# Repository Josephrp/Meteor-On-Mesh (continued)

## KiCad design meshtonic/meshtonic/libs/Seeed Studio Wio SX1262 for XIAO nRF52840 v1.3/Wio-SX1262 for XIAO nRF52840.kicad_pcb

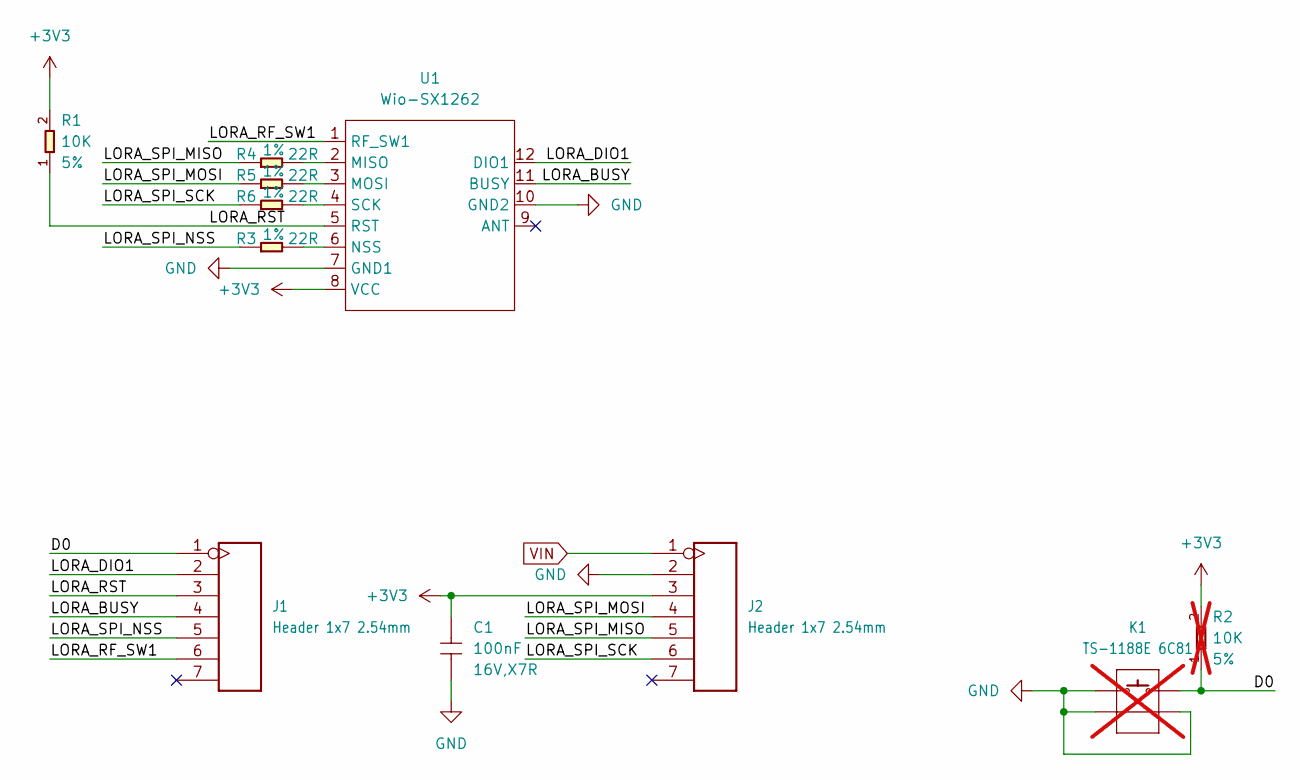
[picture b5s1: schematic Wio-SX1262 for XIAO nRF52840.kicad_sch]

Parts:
C1: 100nF; C0402; Voltage Rating 16V,X7R; MPN CC0402KRX7R7BB104
J1, J2: Header 1x7 2.54mm; H7-2.54; Part Type Header
K1: TS-1188E 6C81; SW4-SMD-7.0X3.5X3.5MM-90D; MPN TS-1188E 6C81; not fitted
R1: 10K; R0402; Power Rating 5%; MPN RC0402JR-0710KL
R2: 10K; R0402; Power Rating 5%; MPN RC0402JR-0710KL; not fitted
R3, R4, R5, R6: 22R; R0402; Power Rating 1%; MPN RC0402FR-0722RL
U1: Wio-SX1262; MODULE12P-1.27-11X11.6MM; MPN Wio-SX1262

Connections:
+3V3: C1.1, J2.3, R1.2, R2.2, U1.8 (VCC)
/D0: J1.1, K1.2, R2.1
/LORA_BUSY: J1.4, U1.11 (BUSY)
/LORA_DIO1: J1.2, U1.12 (DIO1)
/LORA_RF_SW1: J1.6, U1.1 (RF_SW1)
/LORA_RST: J1.3, R1.1, U1.5 (RST)
/LORA_SPI_MISO: J2.5, R4.1
/LORA_SPI_MOSI: J2.4, R5.1
/LORA_SPI_NSS: J1.5, R3.1
/LORA_SPI_SCK: J2.6, R6.1
GND: C1.2, J2.2, K1.1, K1.3 (S1), K1.4 (S2), U1.7 (GND1), U1.10 (GND2)
unnamed: R4.2, U1.2 (MISO)
unnamed: R5.2, U1.3 (MOSI)
unnamed: R3.2, U1.6 (NSS)
unnamed: R6.2, U1.4 (SCK)
VIN: J2.1

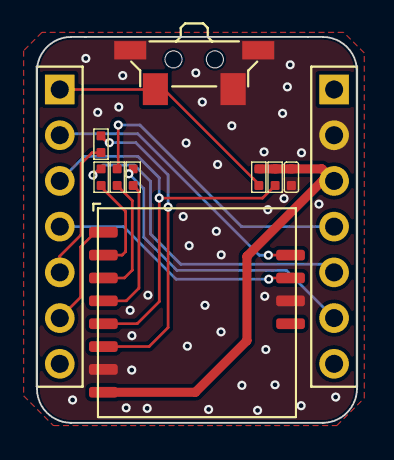
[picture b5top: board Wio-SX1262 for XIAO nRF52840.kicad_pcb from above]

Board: 2 copper layers, 17.8 x 21.4 mm, 11 parts (0 on the bottom side), 15 nets.

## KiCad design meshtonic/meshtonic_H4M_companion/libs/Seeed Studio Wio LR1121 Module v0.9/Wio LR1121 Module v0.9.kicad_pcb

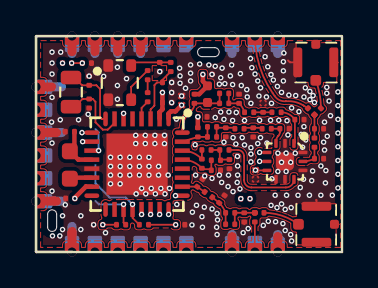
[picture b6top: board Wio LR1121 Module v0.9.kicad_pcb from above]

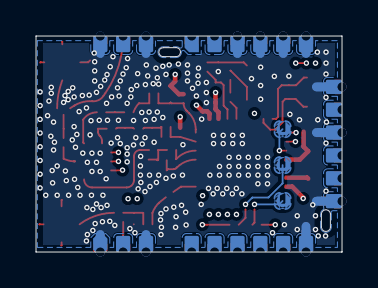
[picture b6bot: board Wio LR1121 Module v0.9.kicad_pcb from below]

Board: 4 copper layers, 17.0 x 12.0 mm, 69 parts (3 on the bottom side), 47 nets.

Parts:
C1, C2, C3, C4, C5, C6, C7, C8, C9, C11, C12, C13, C14, C15, C18, C19, C20, C22, C24, C25, C26, C27, C28, C29, C30, C31, C32, C33, C34, C35, C36, C37, C38, C39, C40, C41, C42, C43: C0201
FB1: L0201
J1, J2: U-FL4P-SMD-1_7X1_7X1_0MM
L1: L0402
L2, L3, L5, L6, L7, L8, L9, L10, L11, L13: L0201
L12: L0603
OSC1: X4_SMD_2_5X2_0MM
R1, R2, R3, R4, R5, R7, R8, R9: R0201
TP23, TP24, TP25: TP35S_SMD
U1: QFN12_0D5_2X2X0_55MM
U2: QFN32_0D5_5X5MM_EP3P3MM
U3: MODULE24_1D27_17X12MM
X1: X2_SMD_2X1_2MM

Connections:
2.4G_RF: C43.2, U3.2
GND_POWER: C3.2, C4.2, C5.2, C6.2, C7.2, C8.2, C11.2, C12.2, C13.2, C14.2, C15.2, C18.2, C19.2, C22.2, C25.2, C26.2, C28.2, C29.2, C30.2, C31.2, C32.2, C33.2, C35.2, C36.2, C37.2, C38.2, C40.2, C42.2, J1.2, J1.3, J1.4, J2.2, J2.3, J2.4, OSC1.1, OSC1.2, U1.2, U1.7, U1.8, U1.10, U1.12, U1.13, U2.13, U2.33, U3.1, U3.3, U3.9, U3.10, U3.13, U3.15, U3.16, U3.17, U3.18, U3.19, U3.22, U3.24
HP_LF: C1.1, L1.2, L2.1, R1.2, U2.32
LP_LF: C9.1, L6.1, L13.2, U2.31
LR1121_BUSY: U2.25, U3.8
LR1121_DIO8: U2.10, U3.11
LR1121_DIO9_INT: U2.9, U3.12
LR1121_RSTN: C42.1, R7.2, U2.6, U3.14
LR1121_SPI_MISO: U2.21, U3.7
LR1121_SPI_MOSI: U2.22, U3.6
LR1121_SPI_NSS: U2.24, U3.4
LR1121_SPI_SCK: U2.23, U3.5
MCU_DIO5: R3.1, TP23.1, U2.20
MCU_DIO6: R2.1, TP24.1, U2.19
MCU_DIO7: R5.1, TP25.1, U2.11
N18704063: C25.1, U2.7, X1.1
N18704080: C26.1, U2.8, X1.2
N18704168: L12.2, U2.14
N18704177: C31.1, L12.1, U2.12
N18704981: C9.2, C37.1, L6.2, L7.1
N18704990: C1.2, C3.1, L2.2, L3.1
N18705097: C2.1, C4.1, L3.2
N18705182: C38.1, C39.1, L7.2
N18705449: C18.1, C39.2, U1.3
N18705460: C2.2, C5.1, U1.1
N18706098: C20.2, C40.1, C41.1, L9.2
N18706198: C41.2, U1.9
N18706539: C24.1, C29.1, L10.2, L11.1
N18706650: C24.2, C27.1, C30.1, C43.1, L11.2
N18706671: C27.2, J2.1
N18712116: C14.1, L5.1, U1.11
N18712319: C36.1, FB1.2, OSC1.4
N18712325: C34.1, OSC1.3
N18712327: C34.2, R4.1
N18713044: C15.1, L5.2, R8.1, R9.1
N18751757: J1.1, R8.2
RFIO_HF: C28.1, L10.1, U2.26
RFI_N: C22.1, L8.2, L9.1, U2.29
RFI_P: C20.1, L8.1, U2.30
RFSW0_V1: C33.1, R3.2, U1.4
RFSW1_V2: C32.1, R2.2, U1.5
RFSW_VDD: C19.1, R5.2, U1.6
SUBG_RF: R9.2, U3.23
VDD_RF: C11.1, C12.1, C13.1, R7.1, U2.2, U2.15, U3.20, U3.21
VR_PA: C6.1, C7.1, C8.1, L1.1, L13.1, R1.1, U2.1
VTCXO: C35.1, FB1.1, U2.3
XTA: R4.2, U2.4

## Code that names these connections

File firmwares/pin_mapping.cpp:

// Seeed XIAO ESP32-S3 Plus — Meshtonic H4M v2 Pinout
//
// Verified against pcb/meshtonic_h4m_v2.kicad_pcb netlist and the official
// Espressif XIAO_ESP32S3_Plus D->GPIO mapping (arduino-esp32 pins_arduino.h /
// Seeed wiki). NOTE: on the Plus, Dn != GPIOn above D5 — the mapping is
// irregular (D11=GPIO38 ... D19=GPIO11), so these constants are the REAL
// silicon GPIO numbers, not the D-label numbers.
//
// Strategy: one shared SPI bus (CLK/MOSI/MISO via the ESP32-S3 GPIO matrix) with
// a separate native-GPIO chip-select per Wio-SX1262 shield, so up to 4 radios
// share SPI2/FSPI. Per-radio BUSY/DIO1 that don't fit on native pins are read
// back through an MCP23017 I2C expander.

// UART0 (freed: console runs on USB-Serial-JTAG)
#define UART0_TX    1   // D0
#define UART0_RX    2   // D1

// Wio-SX1262 chip-selects — native ESP32-S3 GPIO (shared SPI bus)
#define CS_WIO1     3   // D2  (NOTE: GPIO3 is a strapping pin / JTAG sel — output, idle high)
#define CS_WIO2     4   // D3
#define CS_WIO3     10  // D16
#define CS_WIO4     13  // D17

// I2C (native — sensors via TCA9548A, MCP23017, AS5600)
#define I2C_SDA     5   // D4
#define I2C_SCL     6   // D5

// Shared SPI bus (Wio-SX1262 x4 + ILI9341 + microSD), routed via GPIO matrix
#define SPI_MOSI    38  // D11
#define SPI_MISO    39  // D12 (JTAG MTCK — fine without a HW debug probe)
#define SPI_CLK     40  // D13 (JTAG MTDO)

// UART1 (GPS NEO-6M / external)
#define UART1_RX    7   // D8
#define UART1_TX    8   // D9

// TFT (ILI9341) control
#define TFT_DC      43  // D6  (UART0 TXD repurposed)
#define TFT_RST     9   // D10
#define TFT_CS      11  // D19
#define MCP_INT     44  // D7  (UART0 RXD repurposed — MCP23017 INTA to ESP)

// Misc native
#define WIO1_DIO1   12  // D18 (slot-0 DIO1 is native; WIO2..4 DIO1 are on the MCP23017)
#define CS_SD       42  // D15 (JTAG MTMS)
#define ADC_LIGHT   41  // D14 (JTAG MTDI — digital only, NOT ADC-capable: read as GPIO or defer)

// MCP23017 @ 0x20 — GPA bank = per-radio status, GPB bank = shared control + LEDs
// GPA0..3 = WIO1..4 BUSY
// GPA4..6 = WIO2..4 DIO1   (WIO1 DIO1 is native GPIO12 above)
// GPB0    = WIO_RF_SW_EN
// GPB1    = CS_GROVE
// GPB4    = LORA_RST (shared across all 4 radios)
// GPB5..7 = LED_WIO1..3
#define MCP23017_ADDR    0x20
#define MCP_BUSY_WIO1    0   // GPA0
#define MCP_BUSY_WIO2    1   // GPA1
#define MCP_BUSY_WIO3    2   // GPA2
#define MCP_BUSY_WIO4    3   // GPA3
#define MCP_DIO1_WIO2    4   // GPA4
#define MCP_DIO1_WIO3    5   // GPA5
#define MCP_DIO1_WIO4    6   // GPA6
#define MCP_RF_SW_EN     8   // GPB0
#define MCP_LORA_RST     12  // GPB4 (shared)
#define MCP_LED_WIO1     13  // GPB5
#define MCP_LED_WIO2     14  // GPB6
#define MCP_LED_WIO3     15  // GPB7

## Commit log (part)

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2026-06-07 share init for seeedstudio init
2026-06-07 adds silkscreens init
2026-06-14 adds meshtonic board
2026-06-20 adds meshtastic firmware
2026-06-20 adds meshtonic support to esp32PP firmware
2026-06-21 adds meshtonic lora wideband decoder standalone
2026-06-21 adds portapack app
2026-06-21 Vendor mayhem-firmware sources
2026-06-21 Vendor meshtastic and mayhem-firmware as tracked sources
2026-06-23 adds enclosure
2026-06-25 Started mapping out all the compoenents with datasheets where I could find them Yum
2026-06-25 fixes SCL to SDA on J_AS1
2026-06-25 adds grove connectors fix and rerouting
2026-06-26 adds micro vias and solves some issues
2026-06-26 solves some issues
